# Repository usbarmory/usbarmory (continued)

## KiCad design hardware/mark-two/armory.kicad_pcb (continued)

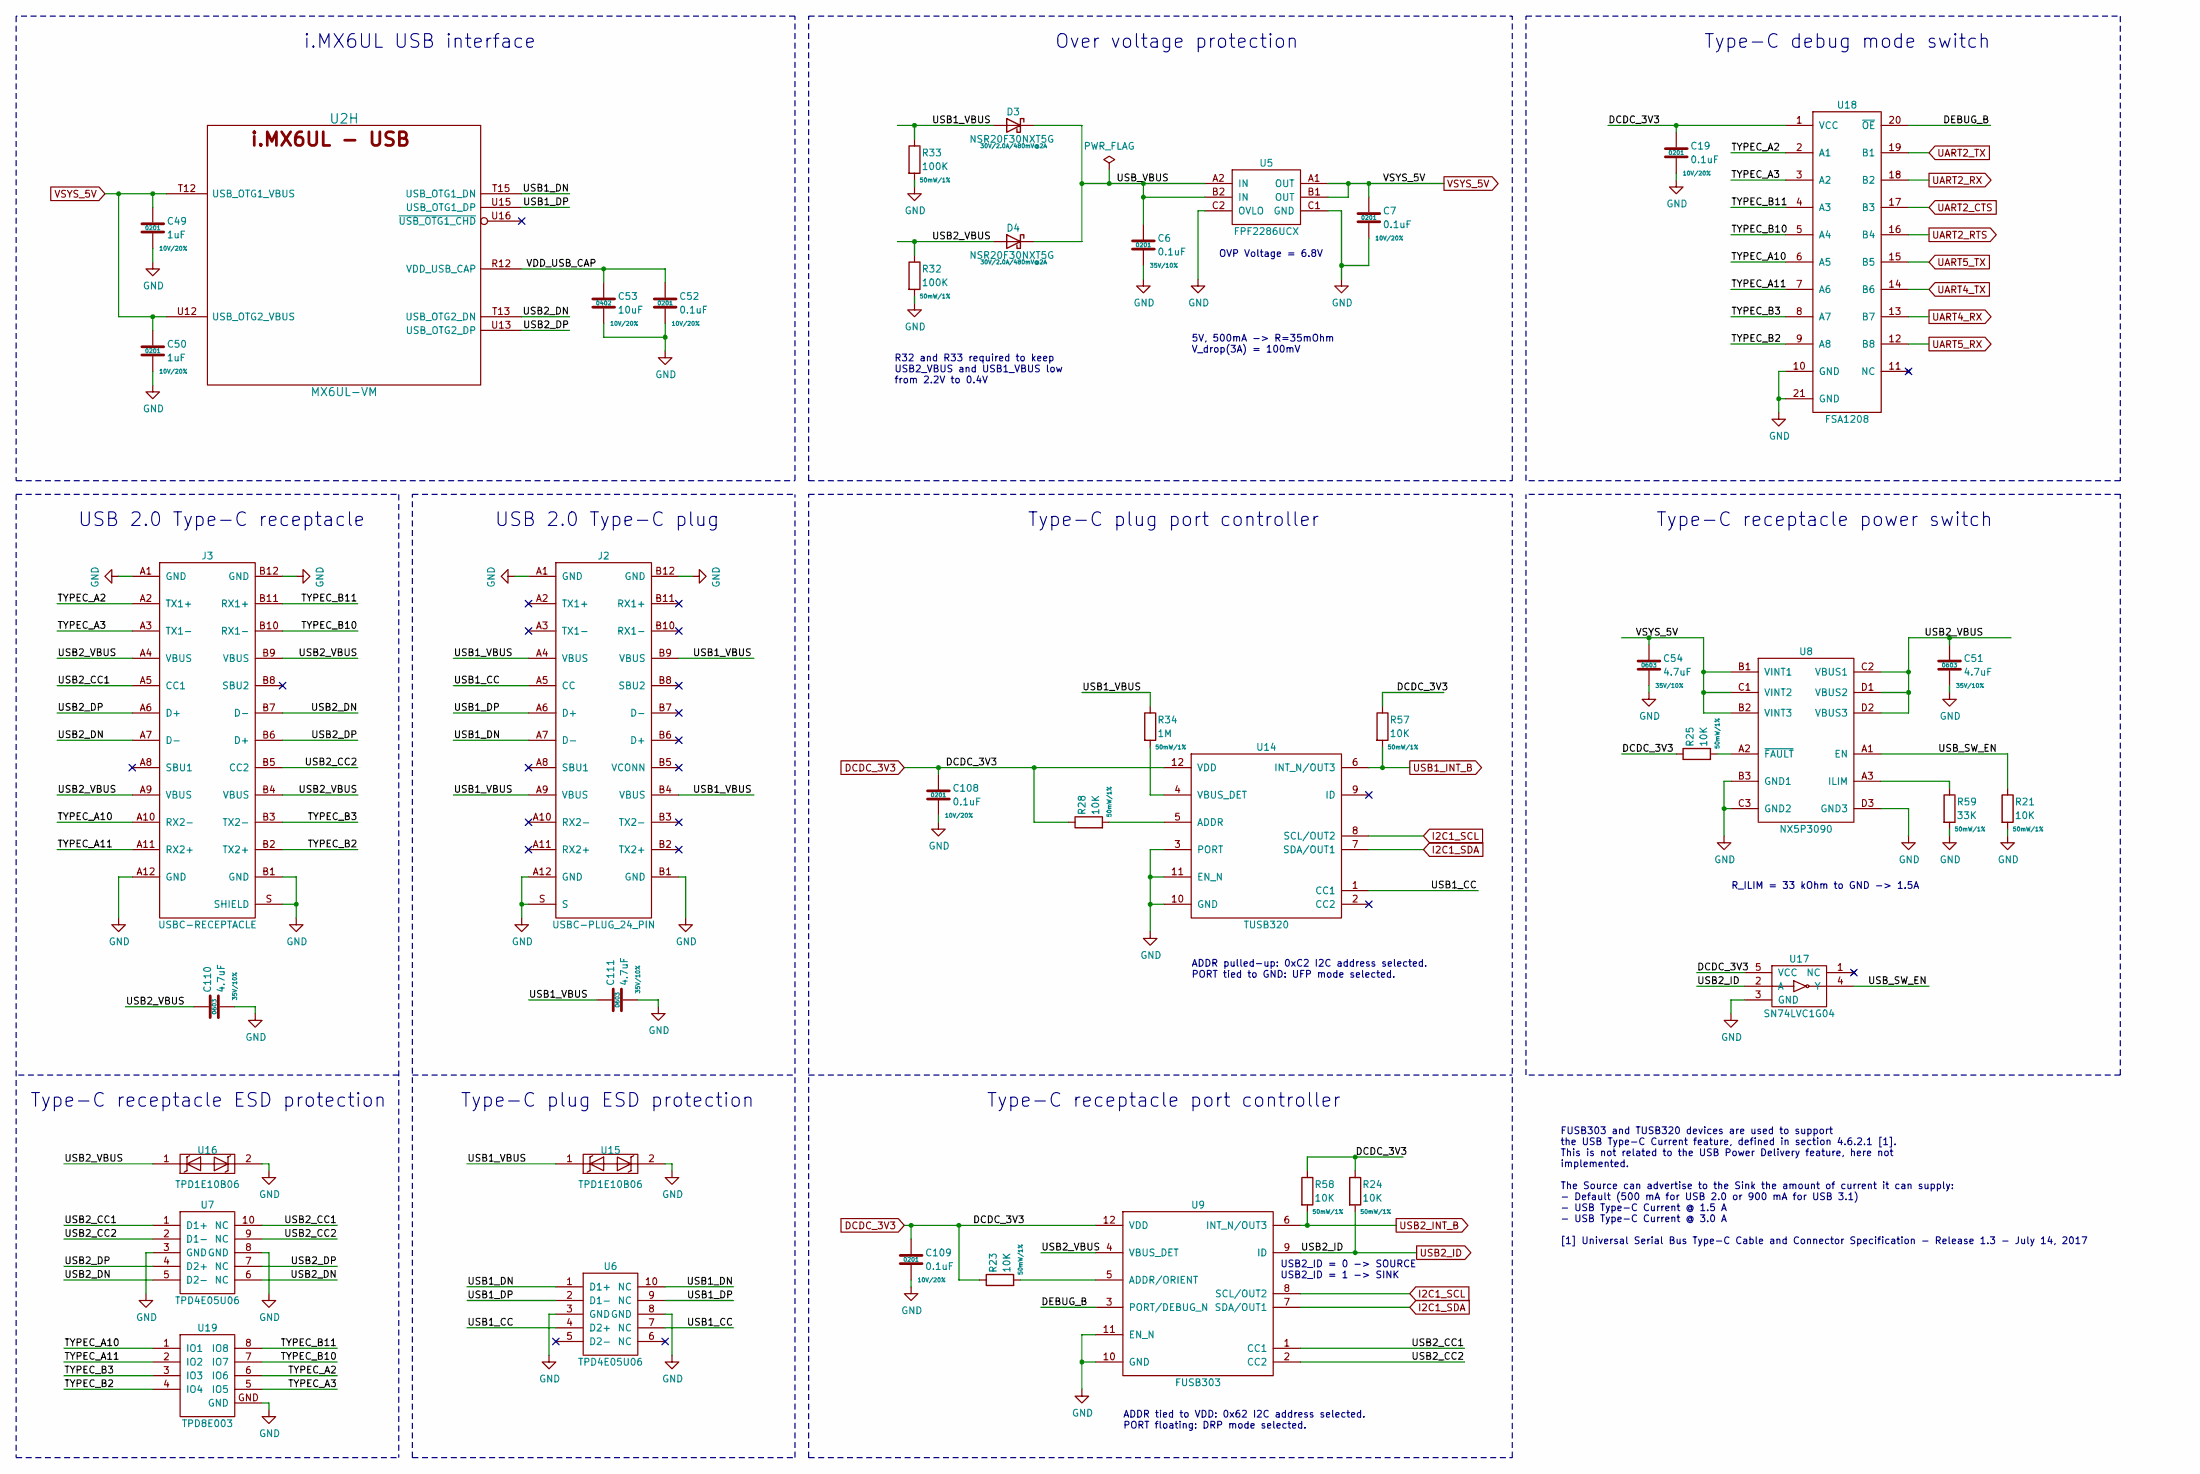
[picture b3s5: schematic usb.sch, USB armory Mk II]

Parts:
C6: 0.1uF; SM0201; Rating 35V/10%; Mfg PN GRM033R61A104ME15D
C7, C19, C52, C108, C109: 0.1uF; SM0201; Rating 10V/20%; Mfg PN GRM033R61A104ME15D
C49, C50: 1uF; SM0201; Rating 10V/20%; Mfg PN GRM033R61A105ME15D
C51, C54, C110, C111: 4.7uF; SM0603; Rating 35V/10%; Mfg PN GRM188R6YA475KE15D
C53: 10uF; SM0402; Rating 10V/20%; Mfg PN CL05A106MP8NUB8
D3, D4: NSR20F30NXT5G; DSN2; Rating 30V/2.0A/480mV@2A; Mfg PN NSR20F30NXT5G
J2: USBC-PLUG_24_PIN; WURTH_632712000112; Mfg PN 632712000112
J3: USBC-RECEPTACLE; MOLEX_105450-0101; Mfg PN 105450-0101
R21, R23, R24, R25, R28, R57, R58: 10K; SM0201; Rating 50mW/1%; Mfg PN CRCW020110K0JNED
R32, R33: 100K; SM0201; Rating 50mW/1%; Mfg PN CRCW0201100KJNED
R34: 1M; SM0201; Rating 50mW/1%; Mfg PN CRCW02011M00FKED
R59: 33K; SM0201; Rating 50mW/1%; Mfg PN CRCW020133K0FKED
U2: MX6UL-VM; SOT1534-2; Mfg PN MCIMX6Z0DVM09AB
U5: FPF2286UCX; WLCSP-6; Mfg PN FPF2286UCX
U6, U7: TPD4E05U06; DQA-USON-10; Mfg PN TPD4E05U06DQAR
U8: NX5P3090; SOT1390-5; Mfg PN NX5P3090UKZ
U9: FUSB303; RWB-QFN-12; Mfg PN FUSB303TMX
U14: TUSB320; RWB-QFN-12; Mfg PN TUSB320IRWBR
U15, U16: TPD1E10B06; X1SON-2; Mfg PN TPD1E10B06DPYR
U17: SN74LVC1G04; X2SON-4; Mfg PN SN74LVC1G04DPWR
U18: FSA1208; MLP-20; Mfg PN FSA1208BQX
U19: TPD8E003; WSON-8; Mfg PN TPD8E003DQDR

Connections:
/USB/DEBUG_B: U9.3 (PORT/DEBUG_N), U18.20 (~OE)
/USB/TYPEC_A2: J3.A2 (TX1+), U18.2 (A1), U19.6 (IO6)
/USB/TYPEC_A3: J3.A3 (TX1-), U18.3 (A2), U19.5 (IO5)
/USB/TYPEC_A10: J3.A10 (RX2-), U18.6 (A5), U19.1 (IO1)
/USB/TYPEC_A11: J3.A11 (RX2+), U18.7 (A6), U19.2 (IO2)
/USB/TYPEC_B2: J3.B2 (TX2+), U18.9 (A8), U19.4 (IO4)
/USB/TYPEC_B3: J3.B3 (TX2-), U18.8 (A7), U19.3 (IO3)
/USB/TYPEC_B10: J3.B10 (RX1-), U18.5 (A4), U19.7 (IO7)
/USB/TYPEC_B11: J3.B11 (RX1+), U18.4 (A3), U19.8 (IO8)
/USB/USB1_CC: J2.A5 (CC), U6.4 (D2+), U6.7 (NC), U14.1 (CC1)
/USB/USB1_DN: J2.A7 (D-), U2.T15 (USB_OTG1_DN), U6.1 (D1+), U6.10 (NC)
/USB/USB1_DP: J2.A6 (D+), U2.U15 (USB_OTG1_DP), U6.2 (D1-), U6.9 (NC)
/USB/USB1_VBUS: C111.1, D3.2 (A), J2.A4 (VBUS), J2.A9 (VBUS), J2.B4 (VBUS), J2.B9 (VBUS), R33.1, R34.1, U15.1
/USB/USB2_CC1: J3.A5 (CC1), U7.1 (D1+), U7.10 (NC), U9.1 (CC1)
/USB/USB2_CC2: J3.B5 (CC2), U7.2 (D1-), U7.9 (NC), U9.2 (CC2)
/USB/USB2_DN: J3.A7 (D-), J3.B7 (D-), U2.T13 (USB_OTG2_DN), U7.5 (D2-), U7.6 (NC)
/USB/USB2_DP: J3.A6 (D+), J3.B6 (D+), U2.U13 (USB_OTG2_DP), U7.4 (D2+), U7.7 (NC)
/USB/USB2_VBUS: C51.1, C110.1, D4.2 (A), J3.A4 (VBUS), J3.A9 (VBUS), J3.B4 (VBUS), J3.B9 (VBUS), R32.1, U8.C2 (VBUS1), U8.D1 (VBUS2), U8.D2 (VBUS3), U9.4 (VBUS_DET), U16.1
/USB/USB_SW_EN: R21.1, U8.A1 (EN), U17.4 (Y)
/USB/USB_VBUS: C6.1, D3.1 (K), D4.1 (K), U5.A2 (IN), U5.B2 (IN)
/USB/VDD_USB_CAP: C52.1, C53.1, U2.R12 (VDD_USB_CAP)
DCDC_3V3: C19.1, C108.1, C109.1, R23.1, R24.1, R25.1, R28.1, R57.1, R58.1, U9.12 (VDD), U14.12 (VDD), U17.5 (VCC), U18.1 (VCC); also elsewhere on the board
GND: C6.2, C7.2, C19.2, C49.2, C50.2, C51.2, C52.2, C53.2, C54.2, C108.2, C109.2, C110.2, C111.2, J2.A1 (GND), J2.A12 (GND), J2.B1 (GND), J2.B12 (GND), J2.S, J3.A1 (GND), J3.A12 (GND), J3.B1 (GND), J3.B12 (GND), J3.S (SHIELD), R21.2, R32.2, R33.2, R59.2, U5.C1 (GND), U5.C2 (OVLO), U6.3 (GND), U6.8 (GND), U7.3 (GND), U7.8 (GND), U8.B3 (GND1), U8.C3 (GND2), U8.D3 (GND3), U9.10 (GND), U9.11 (EN_N), U14.3 (PORT), U14.10 (GND), U14.11 (EN_N), U15.2, U16.2, U17.3 (GND), U18.10 (GND), U18.21 (GND), U19.GND; also elsewhere on the board
I2C1_SCL: U9.8 (SCL/OUT2), U14.8 (SCL/OUT2); also elsewhere on the board
I2C1_SDA: U9.7 (SDA/OUT1), U14.7 (SDA/OUT1); also elsewhere on the board
unnamed: R23.2, U9.5 (ADDR/ORIENT)
unnamed: R25.2, U8.A2 (~FAULT)
unnamed: R28.2, U14.5 (ADDR)
unnamed: R34.2, U14.4 (VBUS_DET)
unnamed: R59.1, U8.A3 (ILIM)
UART2_CTS: U18.17 (B3); also elsewhere on the board
UART2_RTS: U18.16 (B4); also elsewhere on the board
UART2_RX: U18.18 (B2); also elsewhere on the board
UART2_TX: U18.19 (B1); also elsewhere on the board
UART4_RX: U18.13 (B7); also elsewhere on the board
UART4_TX: U18.14 (B6); also elsewhere on the board
UART5_RX: U18.12 (B8); also elsewhere on the board
UART5_TX: U18.15 (B5); also elsewhere on the board
USB1_INT_B: R57.2, U14.6 (INT_N/OUT3); also elsewhere on the board
USB2_ID: R24.2, U9.9 (ID), U17.2 (A); also elsewhere on the board
USB2_INT_B: R58.2, U9.6 (INT_N/OUT3); also elsewhere on the board
VSYS_5V: C7.1, C49.1, C50.1, C54.1, U2.T12 (USB_OTG1_VBUS), U2.U12 (USB_OTG2_VBUS), U5.A1 (OUT), U5.B1 (OUT), U8.B1 (VINT1), U8.B2 (VINT3), U8.C1 (VINT2); also elsewhere on the board

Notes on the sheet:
ADDR tied to VDD: 0x62 I2C address selected. PORT floating: DRP mode selected.
ADDR pulled-up: 0xC2 I2C address selected. PORT tied to GND: UFP mode selected.
FUSB303 and TUSB320 devices are used to support the USB Type-C Current feature, defined in section 4.6.2.1 [1]. This is not related to the USB Power Delivery feature, here not implemented. The Source can advertise to the Sink the amount of current it can supply: - Default (500 mA for USB 2.0 or 900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
USB 2.0 Type-C plug
USB 2.0 Type-C receptacle
R_ILIM = 33 kOhm to GND -> 1.5A
Type-C plug ESD protection
Type-C receptacle ESD protection
Type-C plug port controller
Type-C receptacle port controller
Type-C receptacle power switch
Type-C debug mode switch
OVP Voltage = 6.8V
5V, 500mA -> R=35mOhm V_drop(3A) = 100mV
USB2_ID = 0 -> SOURCE USB2_ID = 1 -> SINK
Over voltage protection
i.MX6UL USB interface
R32 and R33 required to keep USB2_VBUS and USB1_VBUS low from 2.2V to 0.4V

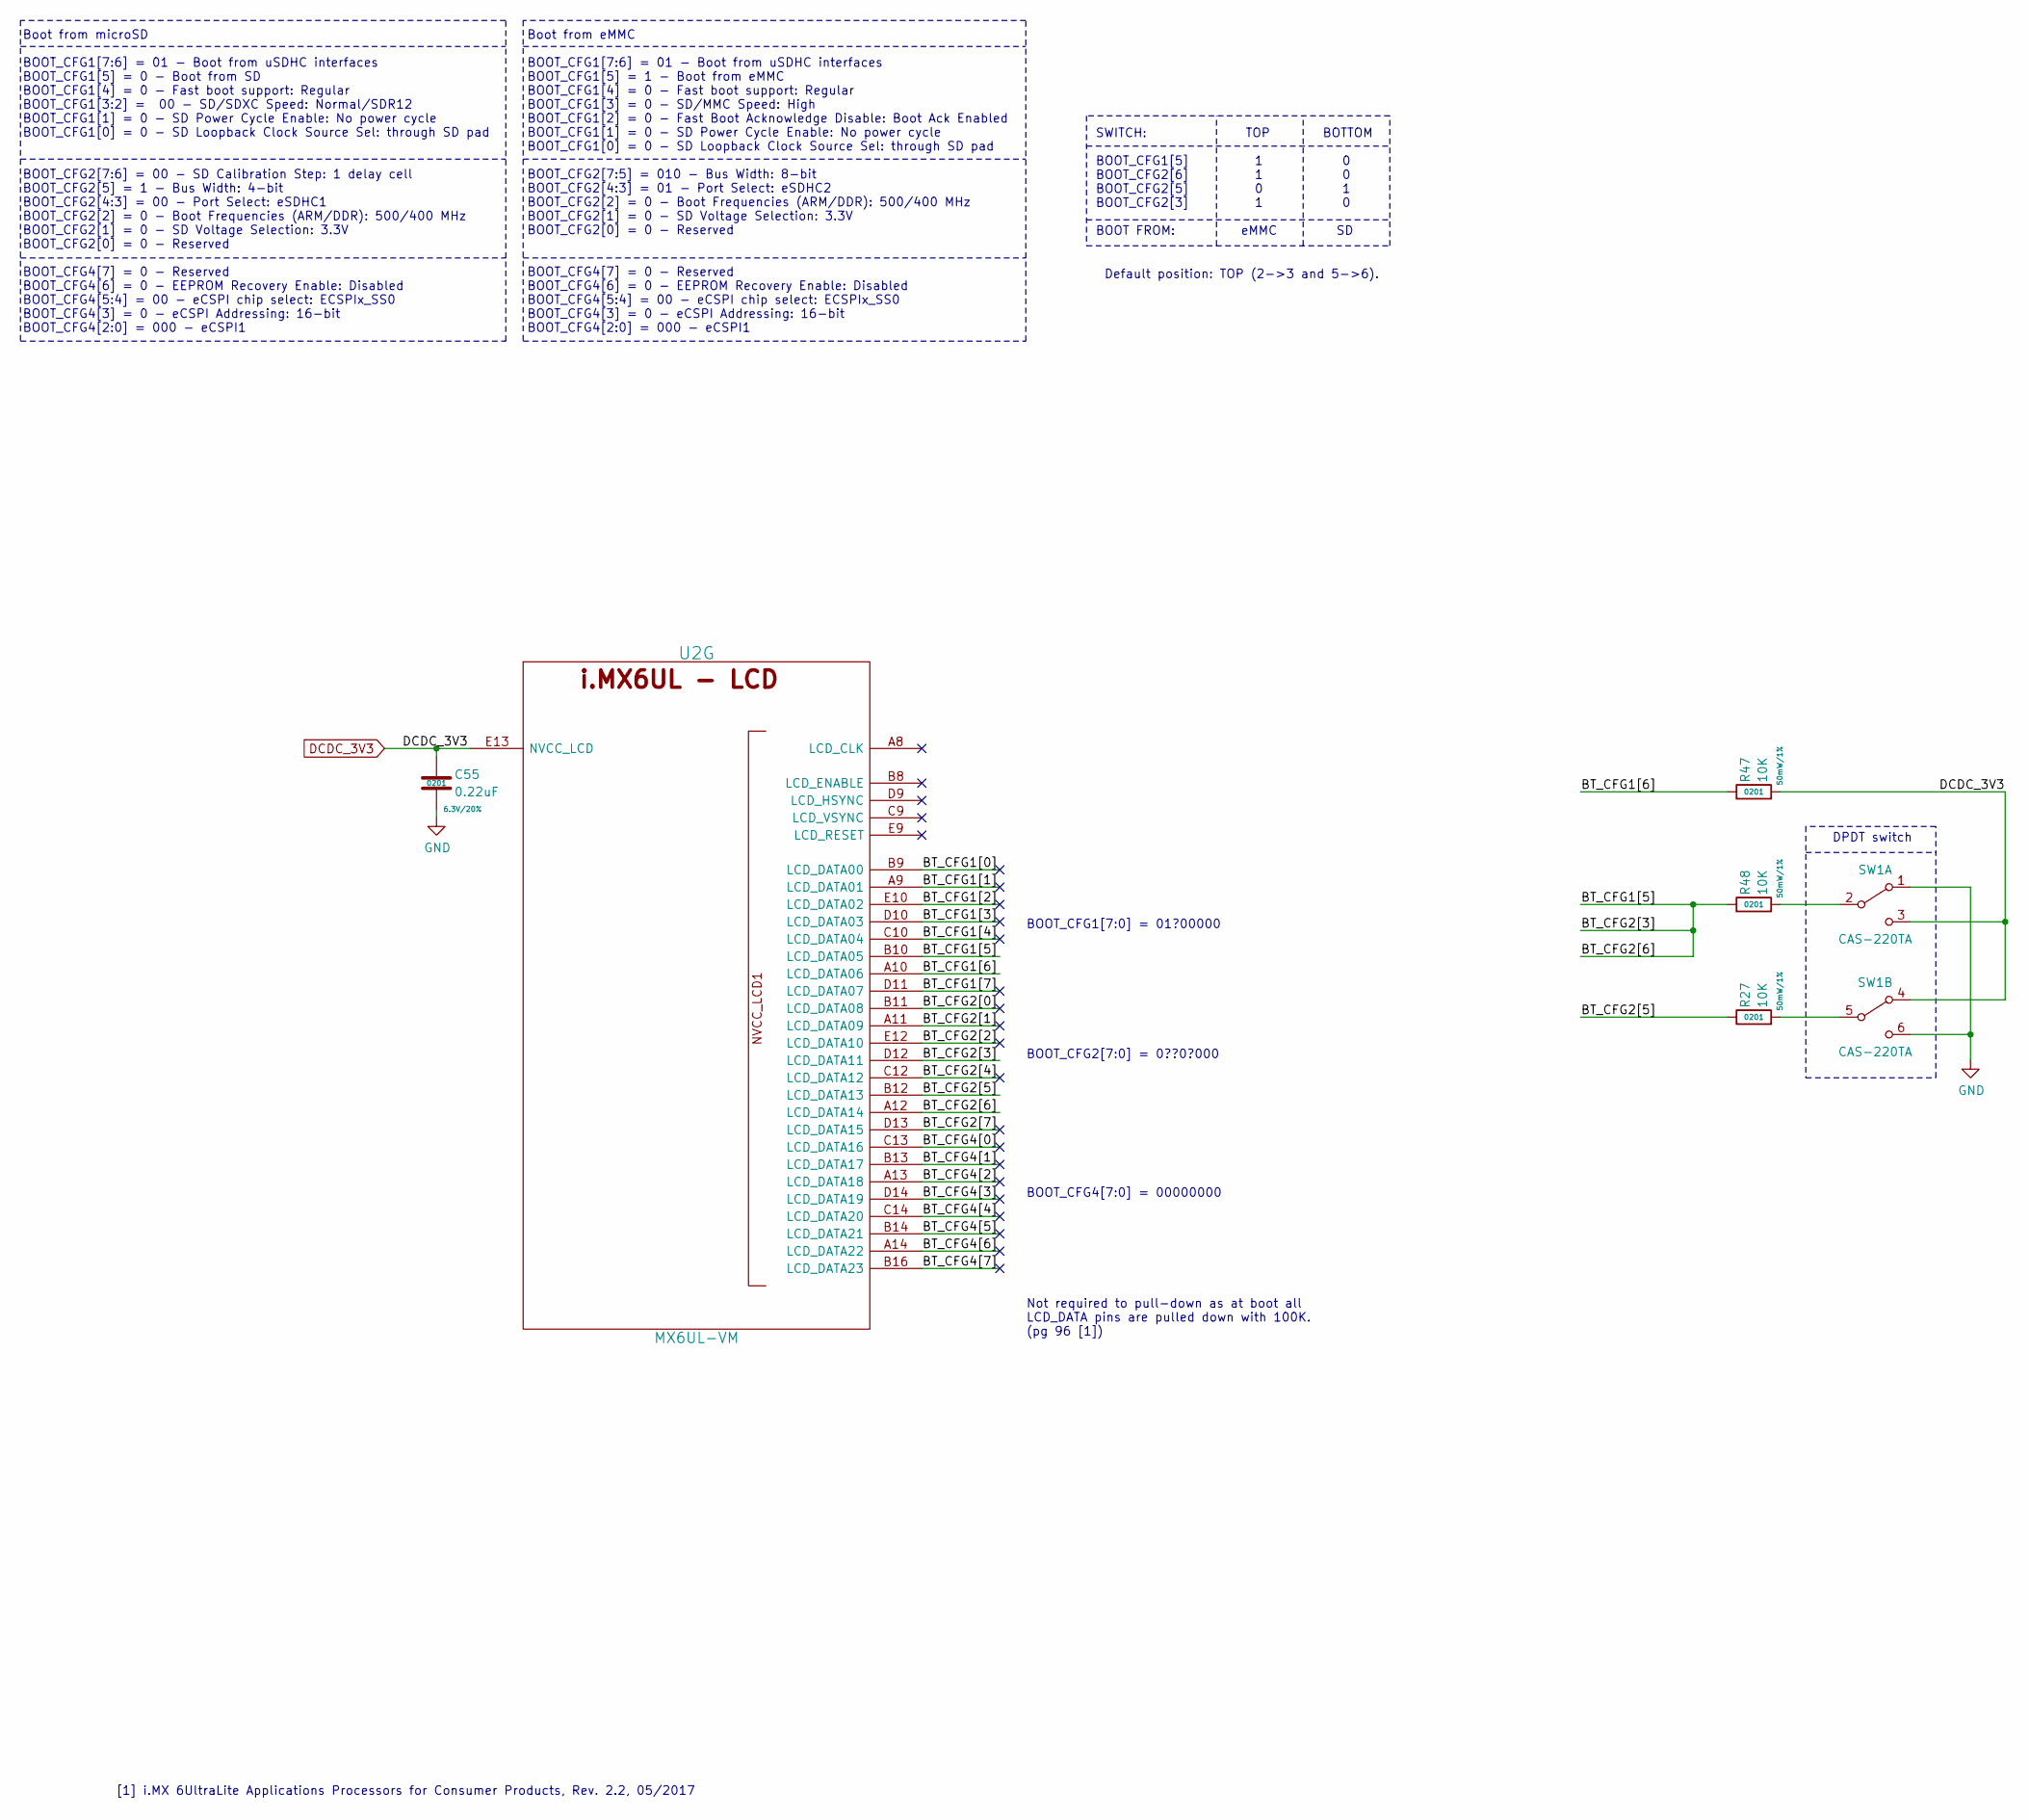
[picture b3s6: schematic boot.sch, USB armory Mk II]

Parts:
C55: 0.22uF; SM0201; Rating 6.3V/20%; Mfg PN GRM033R60J224ME15D
R27, R47, R48: 10K; SM0201; Rating 50mW/1%; Mfg PN CRCW020110K0JNED
SW1: CAS-220TA; CAS-220-A; Mfg PN CAS-220TA
U2: MX6UL-VM; SOT1534-2; Mfg PN MCIMX6Z0DVM09AB

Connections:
/Boot/BT_CFG1[0]: U2.B9 (LCD_DATA00)
/Boot/BT_CFG1[1]: U2.A9 (LCD_DATA01)
/Boot/BT_CFG1[2]: U2.E10 (LCD_DATA02)
/Boot/BT_CFG1[3]: U2.D10 (LCD_DATA03)
/Boot/BT_CFG1[4]: U2.C10 (LCD_DATA04)
/Boot/BT_CFG1[5]: R48.1, U2.A12 (LCD_DATA14), U2.B10 (LCD_DATA05), U2.D12 (LCD_DATA11)
/Boot/BT_CFG1[6]: R47.1, U2.A10 (LCD_DATA06)
/Boot/BT_CFG1[7]: U2.D11 (LCD_DATA07)
/Boot/BT_CFG2[0]: U2.B11 (LCD_DATA08)
/Boot/BT_CFG2[1]: U2.A11 (LCD_DATA09)
/Boot/BT_CFG2[2]: U2.E12 (LCD_DATA10)
/Boot/BT_CFG2[4]: U2.C12 (LCD_DATA12)
/Boot/BT_CFG2[5]: R27.1, U2.B12 (LCD_DATA13)
/Boot/BT_CFG2[7]: U2.D13 (LCD_DATA15)
/Boot/BT_CFG4[0]: U2.C13 (LCD_DATA16)
/Boot/BT_CFG4[1]: U2.B13 (LCD_DATA17)
/Boot/BT_CFG4[2]: U2.A13 (LCD_DATA18)
/Boot/BT_CFG4[3]: U2.D14 (LCD_DATA19)
/Boot/BT_CFG4[4]: U2.C14 (LCD_DATA20)
/Boot/BT_CFG4[5]: U2.B14 (LCD_DATA21)
/Boot/BT_CFG4[6]: U2.A14 (LCD_DATA22)
/Boot/BT_CFG4[7]: U2.B16 (LCD_DATA23)
DCDC_3V3: C55.1, R47.2, SW1.3 (C), SW1.4 (A), U2.E13 (NVCC_LCD); also elsewhere on the board
GND: C55.2, SW1.1 (A), SW1.6 (C); also elsewhere on the board
unnamed: R27.2, SW1.5 (B)
unnamed: R48.2, SW1.2 (B)

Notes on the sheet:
Boot from eMMC BOOT_CFG1[7:6] = 01 - Boot from uSDHC interfaces BOOT_CFG1[5] = 1 - Boot from eMMC BOOT_CFG1[4] = 0 - Fast boot support: Regular BOOT_CFG1[3] = 0 - SD/MMC Speed: High BOOT_CFG1[2] = 0 - Fast Boot Acknowledge Disable: Boot Ack Enabled BOOT_CFG1[1] = 0 - SD Power Cycle Enable: No power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
BOOT_CFG4[7:0] = 00000000
SWITCH: TOP BOTTOM BOOT_CFG1[5] 1 0 BOOT_CFG2[6] 1 0 BOOT_CFG2[5] 0 1 BOOT_CFG2[3] 1 0 BOOT FROM: eMMC SD
BOOT_CFG2[7:0] = 0??0?000
BOOT_CFG1[7:0] = 01?00000
Not required to pull-down as at boot all LCD_DATA pins are pulled down with 100K. (pg 96 [1])
[1] i.MX 6UltraLite Applications Processors for Consumer Products, Rev. 2.2, 05/2017
Boot from microSD BOOT_CFG1[7:6] = 01 - Boot from uSDHC interfaces BOOT_CFG1[5] = 0 - Boot from SD BOOT_CFG1[4] = 0 - Fast boot support: Regular BOOT_CFG1[3:2] = 00 - SD/SDXC Speed: Normal/SDR12 BOOT_CFG1[1] = 0 - SD Power Cycle Enable: No power cycle BOOT_CFG1[0] = 0 - SD Loopback Clock Source Sel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
Default position: TOP (2->3 and 5->6).
DPDT switch

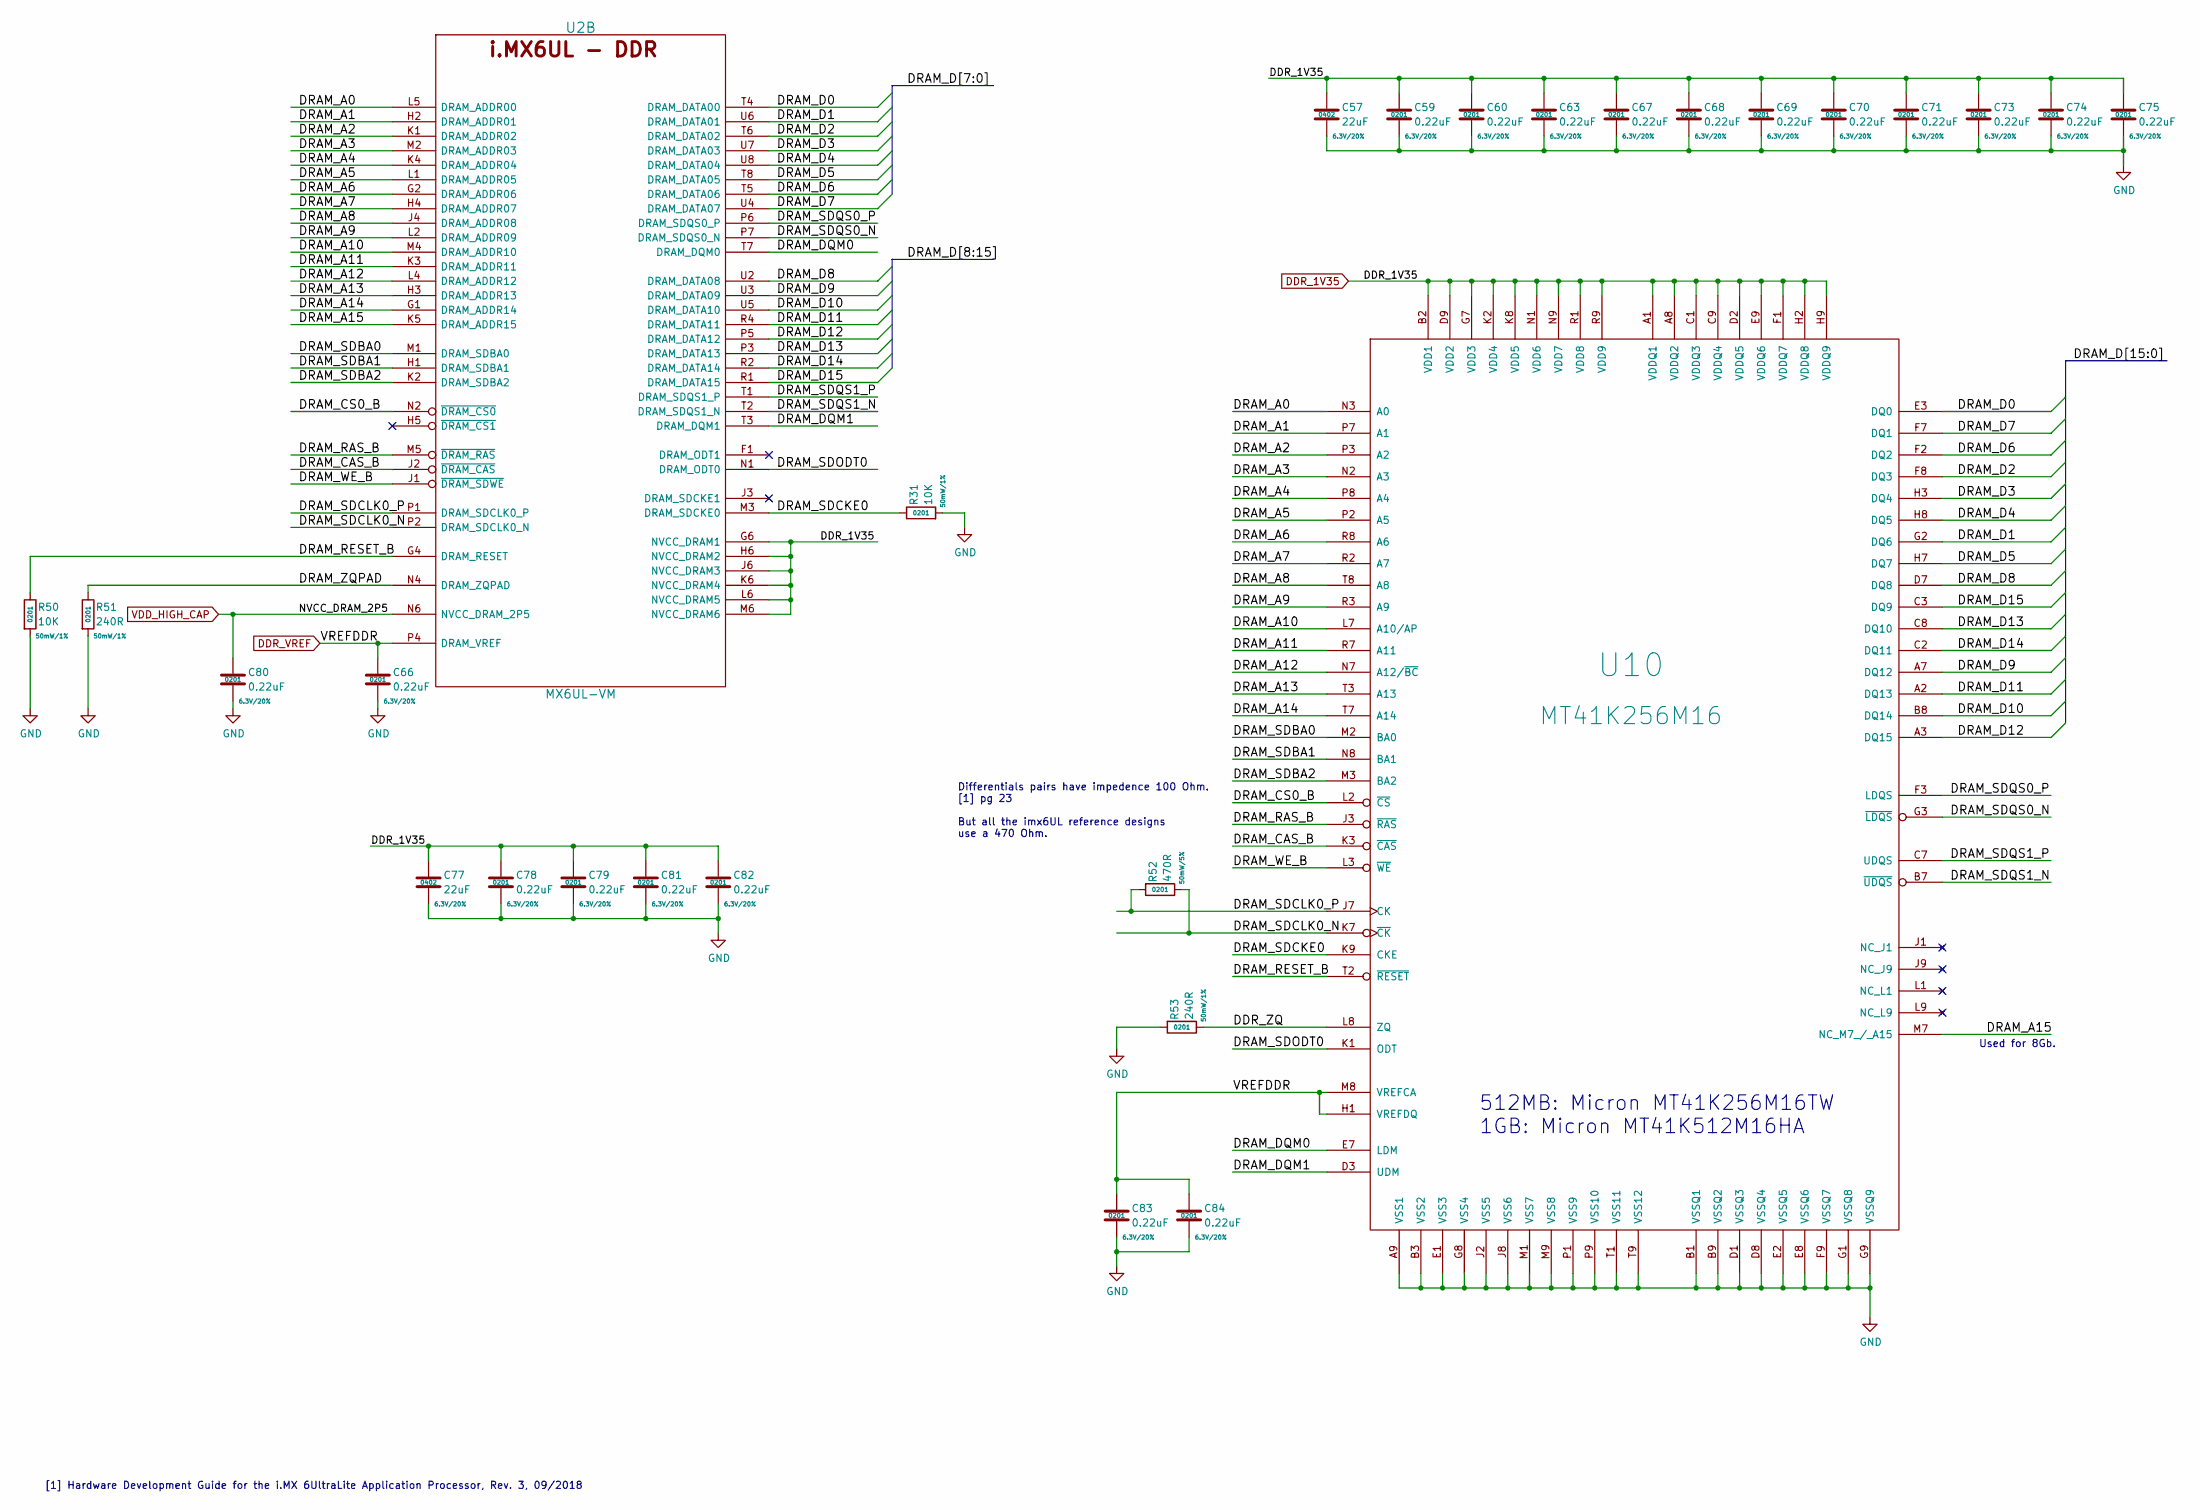
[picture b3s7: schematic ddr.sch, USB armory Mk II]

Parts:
C57, C77: 22uF; SM0402; Rating 6.3V/20%; Mfg PN CL05A226MQ5N6J8
C59, C60, C63, C66, C67, C68, C69, C70, C71, C73, C74, C75, C78, C79, C80, C81, C82, C83, C84: 0.22uF; SM0201; Rating 6.3V/20%; Mfg PN GRM033R60J224ME15D
R31, R50: 10K; SM0201; Rating 50mW/1%; Mfg PN CRCW020110K0JNED
R51, R53: 240R; SM0201; Rating 50mW/1%; Mfg PN CRCW0201240RFNED
R52: 470R; SM0201; Rating 50mW/5%; Mfg PN CRCW0201470RJNED
U2: MX6UL-VM; SOT1534-2; Mfg PN MCIMX6Z0DVM09AB
U10: MT41K256M16; MICRON-FBGA-96; Mfg PN MT41K256M16TW-107:P

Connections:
/DDR/DDR_ZQ: R53.1, U10.L8 (ZQ)
/DDR/DRAM_A0: U2.L5 (DRAM_ADDR00), U10.N3 (A0)
/DDR/DRAM_A1: U2.H2 (DRAM_ADDR01), U10.P7 (A1)
/DDR/DRAM_A2: U2.K1 (DRAM_ADDR02), U10.P3 (A2)
/DDR/DRAM_A3: U2.M2 (DRAM_ADDR03), U10.N2 (A3)
/DDR/DRAM_A4: U2.K4 (DRAM_ADDR04), U10.P8 (A4)
/DDR/DRAM_A5: U2.L1 (DRAM_ADDR05), U10.P2 (A5)
/DDR/DRAM_A6: U2.G2 (DRAM_ADDR06), U10.R8 (A6)
/DDR/DRAM_A7: U2.H4 (DRAM_ADDR07), U10.R2 (A7)
/DDR/DRAM_A8: U2.J4 (DRAM_ADDR08), U10.T8 (A8)
/DDR/DRAM_A9: U2.L2 (DRAM_ADDR09), U10.R3 (A9)
/DDR/DRAM_A10: U2.M4 (DRAM_ADDR10), U10.L7 (A10/AP)
/DDR/DRAM_A11: U2.K3 (DRAM_ADDR11), U10.R7 (A11)
/DDR/DRAM_A12: U2.L4 (DRAM_ADDR12), U10.N7 (A12/~BC)
/DDR/DRAM_A13: U2.H3 (DRAM_ADDR13), U10.T3 (A13)
/DDR/DRAM_A14: U2.G1 (DRAM_ADDR14), U10.T7 (A14)
/DDR/DRAM_A15: U2.K5 (DRAM_ADDR15), U10.M7 (NC_M7_/_A15)
/DDR/DRAM_CAS_B: U2.J2 (~DRAM_CAS), U10.K3 (~CAS)
/DDR/DRAM_CS0_B: U2.N2 (~DRAM_CS0), U10.L2 (~CS)
/DDR/DRAM_D0: U2.T4 (DRAM_DATA00), U10.E3 (DQ0)
/DDR/DRAM_D1: U2.U6 (DRAM_DATA01), U10.G2 (DQ6)
/DDR/DRAM_D2: U2.T6 (DRAM_DATA02), U10.F8 (DQ3)
/DDR/DRAM_D3: U2.U7 (DRAM_DATA03), U10.H3 (DQ4)
/DDR/DRAM_D4: U2.U8 (DRAM_DATA04), U10.H8 (DQ5)
/DDR/DRAM_D5: U2.T8 (DRAM_DATA05), U10.H7 (DQ7)
/DDR/DRAM_D6: U2.T5 (DRAM_DATA06), U10.F2 (DQ2)
/DDR/DRAM_D7: U2.U4 (DRAM_DATA07), U10.F7 (DQ1)
/DDR/DRAM_D8: U2.U2 (DRAM_DATA08), U10.D7 (DQ8)
/DDR/DRAM_D9: U2.U3 (DRAM_DATA09), U10.A7 (DQ12)
/DDR/DRAM_D10: U2.U5 (DRAM_DATA10), U10.B8 (DQ14)
/DDR/DRAM_D11: U2.R4 (DRAM_DATA11), U10.A2 (DQ13)
/DDR/DRAM_D12: U2.P5 (DRAM_DATA12), U10.A3 (DQ15)
/DDR/DRAM_D13: U2.P3 (DRAM_DATA13), U10.C8 (DQ10)
/DDR/DRAM_D14: U2.R2 (DRAM_DATA14), U10.C2 (DQ11)
/DDR/DRAM_D15: U2.R1 (DRAM_DATA15), U10.C3 (DQ9)
/DDR/DRAM_DQM0: U2.T7 (DRAM_DQM0), U10.E7 (LDM)
/DDR/DRAM_DQM1: U2.T3 (DRAM_DQM1), U10.D3 (UDM)
/DDR/DRAM_RAS_B: U2.M5 (~DRAM_RAS), U10.J3 (~RAS)
/DDR/DRAM_RESET_B: R50.1, U2.G4 (DRAM_RESET), U10.T2 (~RESET)
/DDR/DRAM_SDBA0: U2.M1 (DRAM_SDBA0), U10.M2 (BA0)
/DDR/DRAM_SDBA1: U2.H1 (DRAM_SDBA1), U10.N8 (BA1)
/DDR/DRAM_SDBA2: U2.K2 (DRAM_SDBA2), U10.M3 (BA2)
/DDR/DRAM_SDCKE0: R31.1, U2.M3 (DRAM_SDCKE0), U10.K9 (CKE)
/DDR/DRAM_SDCLK0_N: R52.1, U2.P2 (DRAM_SDCLK0_N), U10.K7 (~CK)
/DDR/DRAM_SDCLK0_P: R52.2, U2.P1 (DRAM_SDCLK0_P), U10.J7 (CK)
/DDR/DRAM_SDODT0: U2.N1 (DRAM_ODT0), U10.K1 (ODT)
/DDR/DRAM_SDQS0_N: U2.P7 (DRAM_SDQS0_N), U10.G3 (~LDQS)
/DDR/DRAM_SDQS0_P: U2.P6 (DRAM_SDQS0_P), U10.F3 (LDQS)
/DDR/DRAM_SDQS1_N: U2.T2 (DRAM_SDQS1_N), U10.B7 (~UDQS)
/DDR/DRAM_SDQS1_P: U2.T1 (DRAM_SDQS1_P), U10.C7 (UDQS)
/DDR/DRAM_WE_B: U2.J1 (~DRAM_SDWE), U10.L3 (~WE)
/DDR/DRAM_ZQPAD: R51.1, U2.N4 (DRAM_ZQPAD)
DDR_1V35: C57.1, C59.1, C60.1, C63.1, C67.1, C68.1, C69.1, C70.1, C71.1, C73.1, C74.1, C75.1, C77.1, C78.1, C79.1, C81.1, C82.1, U2.G6 (NVCC_DRAM1), U2.H6 (NVCC_DRAM2), U2.J6 (NVCC_DRAM3), U2.K6 (NVCC_DRAM4), U2.L6 (NVCC_DRAM5), U2.M6 (NVCC_DRAM6), U10.A1 (VDDQ1), U10.A8 (VDDQ2), U10.B2 (VDD1), U10.C1 (VDDQ3), U10.C9 (VDDQ4), U10.D2 (VDDQ5), U10.D9 (VDD2), U10.E9 (VDDQ6), U10.F1 (VDDQ7), U10.G7 (VDD3), U10.H2 (VDDQ8), U10.H9 (VDDQ9), U10.K2 (VDD4), U10.K8 (VDD5), U10.N1 (VDD6), U10.N9 (VDD7), U10.R1 (VDD8), U10.R9 (VDD9); also elsewhere on the board
DDR_VREF: C66.1, C83.1, C84.1, U2.P4 (DRAM_VREF), U10.H1 (VREFDQ), U10.M8 (VREFCA); also elsewhere on the board
GND: C57.2, C59.2, C60.2, C63.2, C66.2, C67.2, C68.2, C69.2, C70.2, C71.2, C73.2, C74.2, C75.2, C77.2, C78.2, C79.2, C80.2, C81.2, C82.2, C83.2, C84.2, R31.2, R50.2, R51.2, R53.2, U10.A9 (VSS1), U10.B1 (VSSQ1), U10.B3 (VSS2), U10.B9 (VSSQ2), U10.D1 (VSSQ3), U10.D8 (VSSQ4), U10.E1 (VSS3), U10.E2 (VSSQ5), U10.E8 (VSSQ6), U10.F9 (VSSQ7), U10.G1 (VSSQ8), U10.G8 (VSS4), U10.G9 (VSSQ9), U10.J2 (VSS5), U10.J8 (VSS6), U10.M1 (VSS7), U10.M9 (VSS8), U10.P1 (VSS9), U10.P9 (VSS10), U10.T1 (VSS11), U10.T9 (VSS12); also elsewhere on the board
VDD_HIGH_CAP: C80.1, U2.N6 (NVCC_DRAM_2P5); also elsewhere on the board

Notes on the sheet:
Used for 8Gb.
512MB: Micron MT41K256M16TW 1GB: Micron MT41K512M16HA
[1] Hardware Development Guide for the i.MX 6UltraLite Application Processor, Rev. 3, 09/2018
Differentials pairs have impedence 100 Ohm. [1] pg 23 But all the imx6UL reference designs use a 470 Ohm.
